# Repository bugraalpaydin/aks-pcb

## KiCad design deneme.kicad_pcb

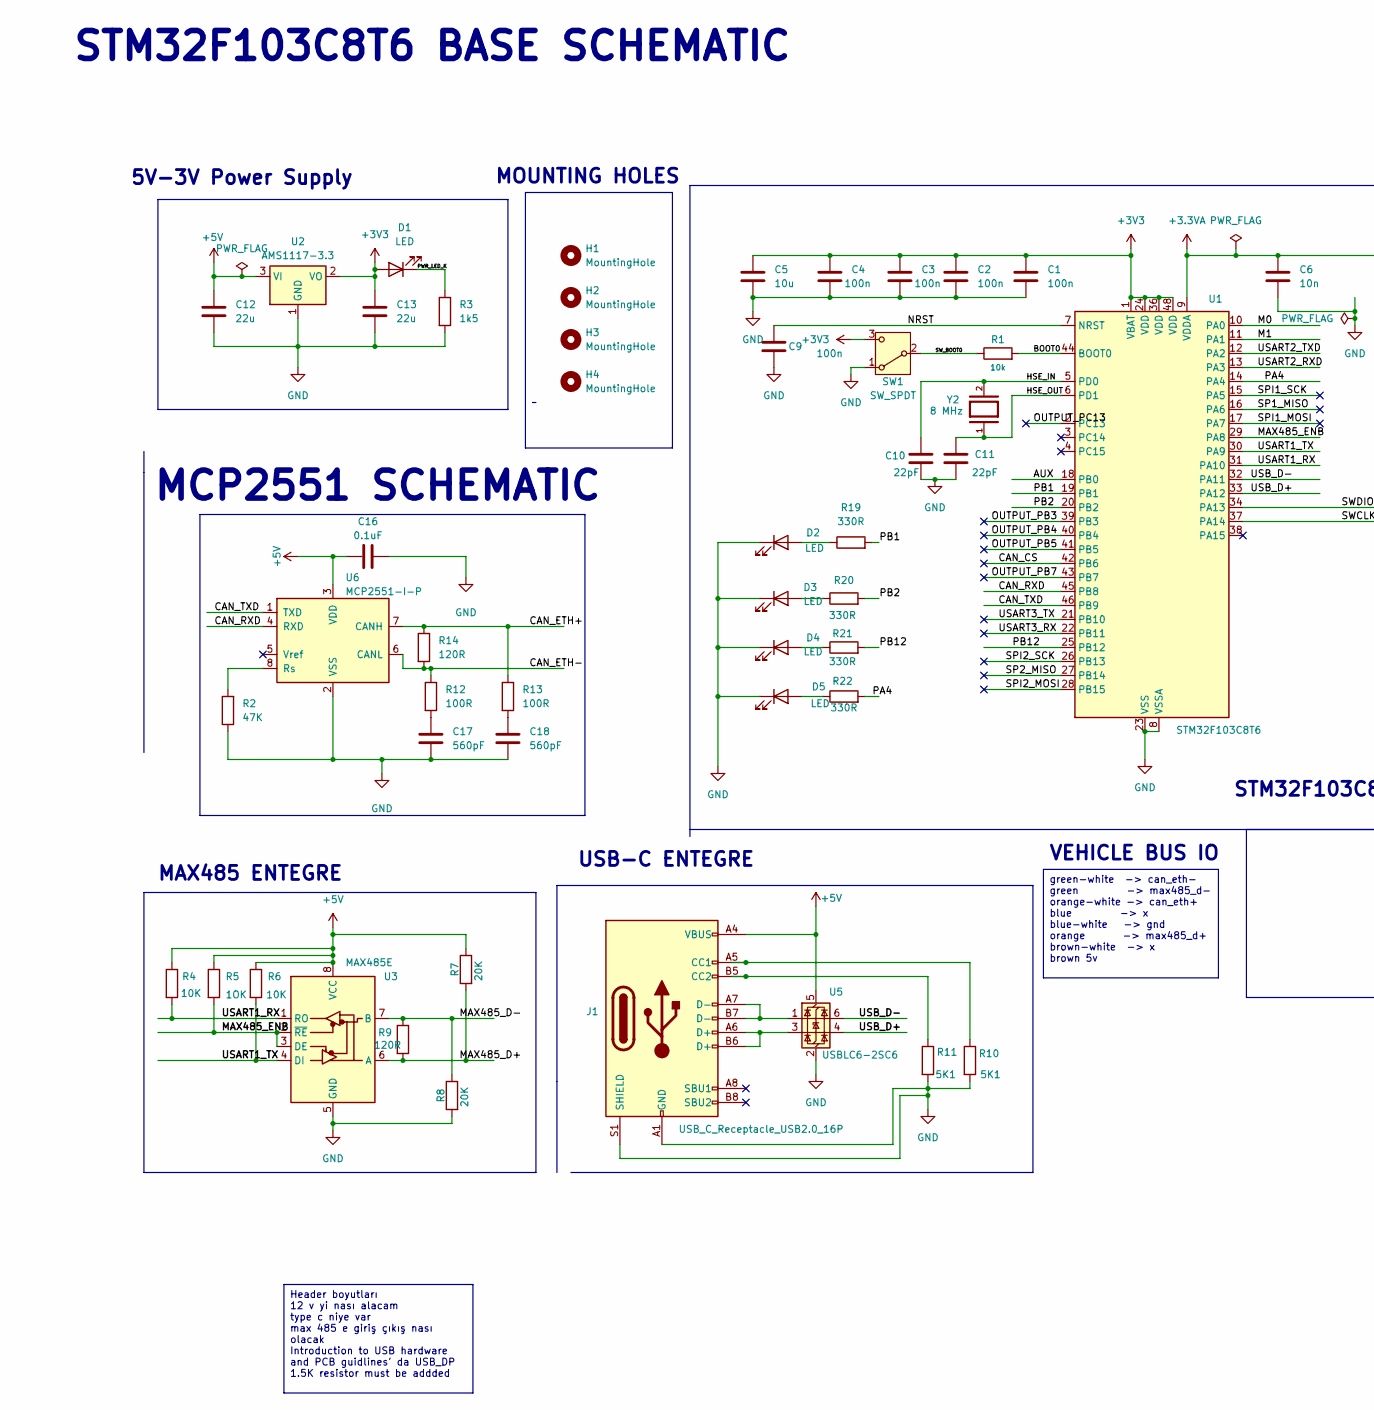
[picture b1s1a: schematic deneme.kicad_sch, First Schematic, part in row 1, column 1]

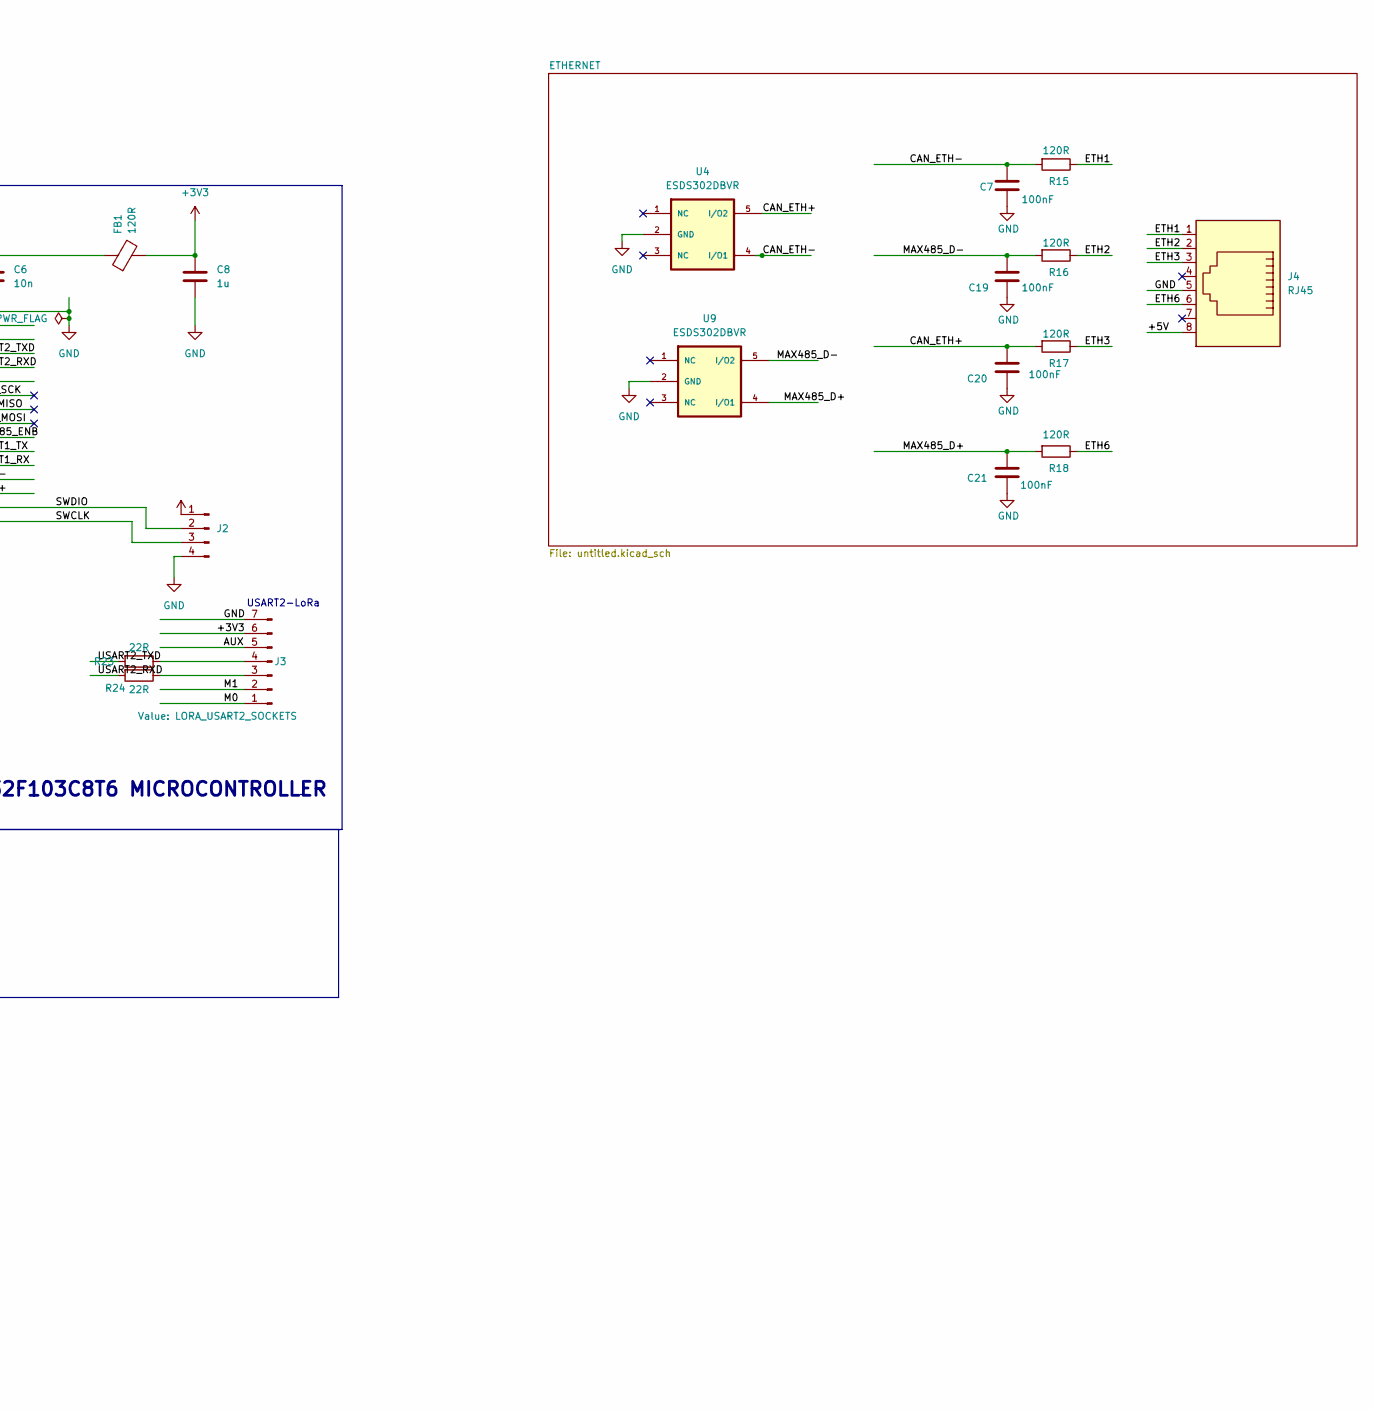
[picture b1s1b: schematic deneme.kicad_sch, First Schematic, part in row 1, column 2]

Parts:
C1, C2, C3, C4, C9: 100n; C_1206_3216Metric
C5: 10u; C_1206_3216Metric
C6: 10n; C_1206_3216Metric
C7, C19, C20, C21: 100nF; C_1206_3216Metric
C8: 1u; C_1206_3216Metric
C10, C11: 22pF; C_1206_3216Metric
C12, C13: 22u; C_1206_3216Metric
C16: 0.1uF; C_1206_3216Metric
C17, C18: 560pF; C_1206_3216Metric
D1, D2, D3, D4, D5: LED; LED_1206_3216Metric
FB1: 120R; L_1206_3216Metric
H1, H2, H3, H4: MountingHole; MountingHole_2.1mm
J1: USB_C_Receptacle_USB2.0_16P; USB-C
J2: Conn_01x04_Pin; PinHeader_1x04_P2.54mm_Vertical
J3: LORA_USART2_SOCKETS; PinSocket_1x07_P2.54mm_Vertical
J4: RJ45; RJ45_Amphenol_RJHSE538X
R1: 10k; R_1206_3216Metric
R2: 47K; R_1206_3216Metric
R3: 1k5; R_1206_3216Metric
R4, R6: 10K; R_1206_3216Metric
R5: 1OK; R_1206_3216Metric
R7, R8: 20K; R_1206_3216Metric
R9, R14: 120R; R_1206_3216Metric
R10, R11: 5K1; R_1206_3216Metric
R12, R13: 100R; R_1206_3216Metric
R15, R16, R17, R18: 120R; C_1206_3216Metric
R19, R20, R21, R22: 330R; R_1206_3216Metric
R23, R24: 22R; R_1206_3216Metric
SW1: SW_SPDT; SW_CK_JS202011CQN_DPDT_Straight
U1: STM32F103C8T6; LQFP-48_7x7mm_P0.5mm
U2: AMS1117-3.3; SOT-223-3_TabPin2
U3: MAX485E; DIP-8_W8.89mm_SMDSocket_LongPads
U4, U9: ESDS302DBVR; ESDS302
U5: USBLC6-2SC6; SOT-23-6
U6: MCP2551-I-P; DIP-8_W7.62mm
Y2: 8 MHz; XTAL_HC49P488W43L1150T466H350; PARTREV 1.0

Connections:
+3.3VA: C6.1, FB1.1, U1.9 (VDDA)
+3V3: C1.1, C2.1, C3.1, C4.1, C5.1, C8.1, C13.1, D1.2 (A), FB1.2, J2.1, J3.6, SW1.3 (C), U1.1 (VBAT), U1.24 (VDD), U1.36 (VDD), U1.48 (VDD), U2.2 (VO)
+5V: C12.1, C16.1, J1.A4 (VBUS), J1.A9 (VBUS), J1.B4 (VBUS), J1.B9 (VBUS), J4.8, R4.1, R5.1, R6.1, R7.1, U2.3 (VI), U3.8 (VCC), U5.5 (VBUS), U6.3 (VDD)
/AUX: J3.5, U1.18 (PB0)
/BOOT0: R1.2, U1.44 (BOOT0)
/CAN_CS: U1.42 (PB6)
/CAN_ETH+: C20.1, R13.1, R14.1, R17.2, U4.5 (I/O2), U6.7 (CANH)
/CAN_ETH-: C7.1, R12.1, R14.2, R15.2, U4.4 (I/O1), U6.6 (CANL)
/CAN_RXD: U1.45 (PB8), U6.4 (RXD)
/CAN_TXD: U1.46 (PB9), U6.1 (TXD)
/ETH1: J4.1, R15.1
/ETH2: J4.2, R16.1
/ETH3: J4.3, R17.1
/ETH6: J4.6, R18.1
/HSE_IN: C10.1, U1.5 (PD0), Y2.2
/HSE_OUT: C11.1, U1.6 (PD1), Y2.1
/M0: J3.1, U1.10 (PA0)
/M1: J3.2, U1.11 (PA1)
/MAX485_D+: C21.1, R7.2, R9.2, R18.2, U3.6 (A), U9.4 (I/O1)
/MAX485_D-: C19.1, R8.1, R9.1, R16.2, U3.7 (B), U9.5 (I/O2)
/MAX485_ENB: R5.2, U1.29 (PA8), U3.2 (~RE), U3.3 (DE)
/NRST: C9.1, U1.7 (NRST)
/OUTPUT_PB3: U1.39 (PB3)
/OUTPUT_PB4: U1.40 (PB4)
/OUTPUT_PB5: U1.41 (PB5)
/OUTPUT_PB7: U1.43 (PB7)
/OUTPUT_PC13: U1.2 (PC13)
/PA4: R22.2, U1.14 (PA4)
/PB1: R19.2, U1.19 (PB1)
/PB2: R20.2, U1.20 (PB2)
/PB12: R21.2, U1.25 (PB12)
/PWR_LED_K: D1.1 (K), R3.1
/SP1_MISO: U1.16 (PA6)
/SP2_MISO: U1.27 (PB14)
/SPI1_MOSI: U1.17 (PA7)
/SPI1_SCK: U1.15 (PA5)
/SPI2_MOSI: U1.28 (PB15)
/SPI2_SCK: U1.26 (PB13)
/SWCLK: J2.3, U1.37 (PA14)
/SWDIO: J2.2, U1.34 (PA13)
/SW_BOOT0: R1.1, SW1.2 (B)
/USART1_RX: R4.2, U1.31 (PA10), U3.1 (RO)
/USART1_TX: R6.2, U1.30 (PA9), U3.4 (DI)
/USART2_RXD: R24.2, U1.13 (PA3)
/USART2_TXD: R23.2, U1.12 (PA2)
/USART3_RX: U1.22 (PB11)
/USART3_TX: U1.21 (PB10)
/USB_D+: U1.33 (PA12), U5.4 (I/O2)
/USB_D-: U1.32 (PA11), U5.6 (I/O1)
GND: C1.2, C2.2, C3.2, C4.2, C5.2, C6.2, C7.2, C8.2, C9.2, C10.2, C11.2, C12.2, C13.2, C16.2, C17.2, C18.2, C19.2, C20.2, C21.2, D2.1 (K), D3.1 (K), D4.1 (K), D5.1 (K), J1.A1 (GND), J1.A12 (GND), J1.B1 (GND), J1.B12 (GND), J1.S1 (SHIELD), J2.4, J3.7, J4.5, R2.1, R3.2, R8.2, R10.2, R11.2, SW1.1 (A), U1.8 (VSSA), U1.23 (VSS), U1.35 (VSS), U1.47 (VSS), U2.1 (GND), U3.5 (GND), U4.2 (GND), U5.2 (GND), U6.2 (VSS), U9.2 (GND)
unnamed: C17.1, R12.2
unnamed: C18.1, R13.2
unnamed: D2.2 (A), R19.1
unnamed: D3.2 (A), R20.1
unnamed: D4.2 (A), R21.1
unnamed: D5.2 (A), R22.1
unnamed: J1.A5 (CC1), R10.1
unnamed: J1.B5 (CC2), R11.1
unnamed: J1.A6 (D+), J1.B6 (D+), U5.3 (I/O2)
unnamed: J1.A7 (D-), J1.B7 (D-), U5.1 (I/O1)
unnamed: J3.3, R24.1
unnamed: J3.4, R23.1
unnamed: R2.2, U6.8 (Rs)

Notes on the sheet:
green-white -> can_eth- green -> max485_d- orange-white -> can_eth+ blue -> x blue-white -> gnd orange -> max485_d+ brown-white -> x brown 5v
Header boyutları 12 v yi nası alacam type c niye var max 485 e giriş çıkış nası olacak Introduction to USB hardware and PCB guidlines' da USB_DP 1.5K resistor must be addded
5V-3V Power Supply
USB-C ENTEGRE
VEHICLE BUS IO
STM32F103C8T6 BASE SCHEMATIC
MOUNTING HOLES
MAX485 ENTEGRE
STM32F103C8T6 MICROCONTROLLER
USART2-LoRa
MCP2551 SCHEMATIC

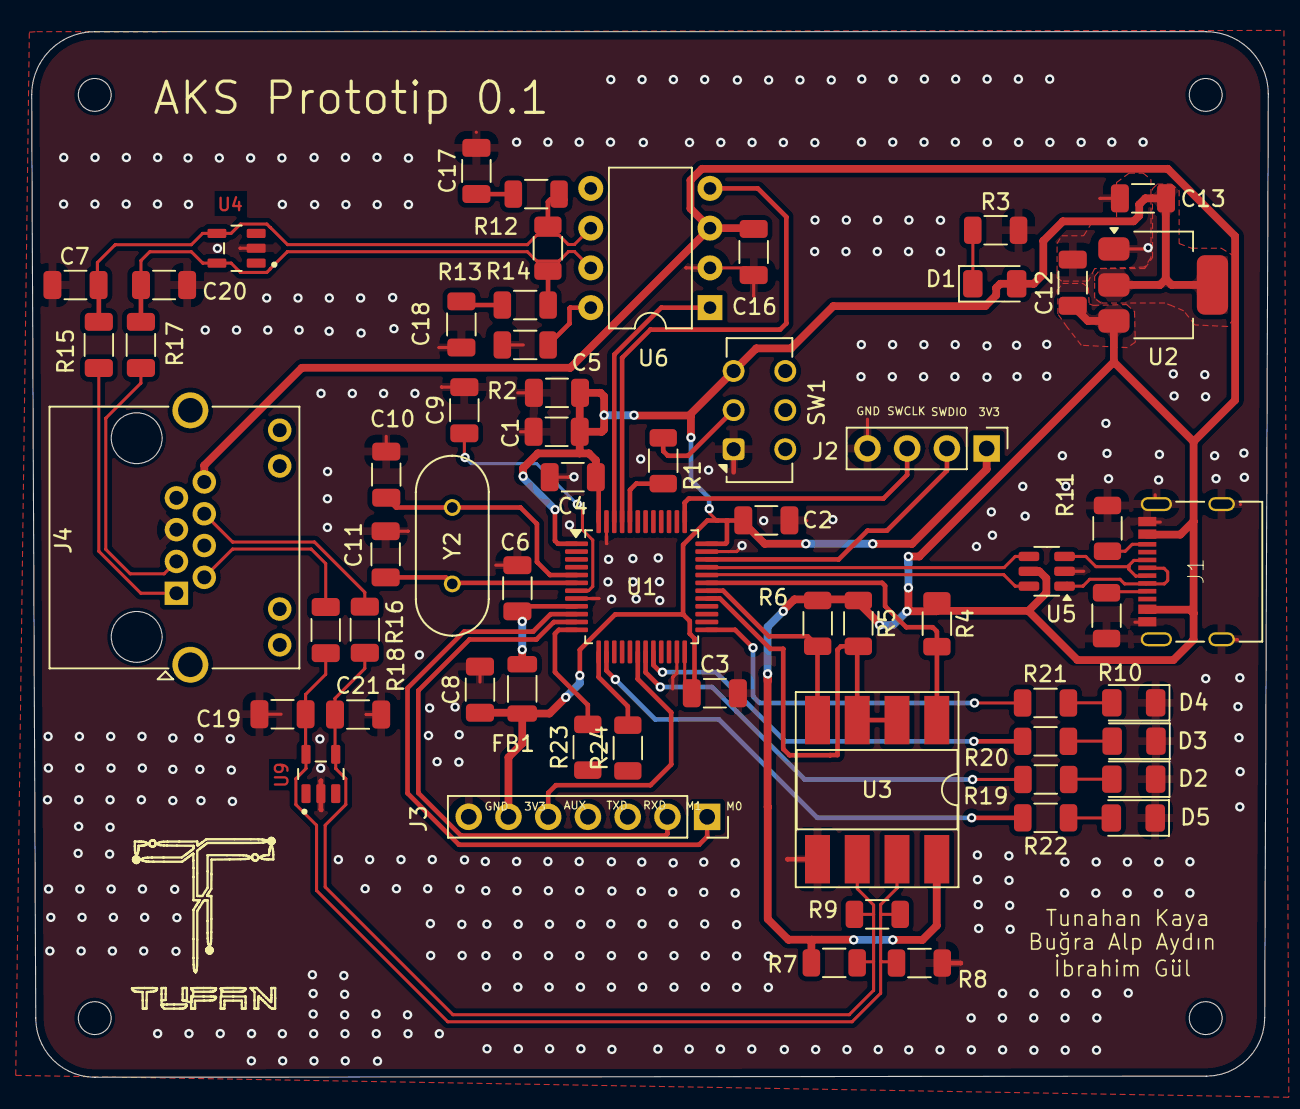
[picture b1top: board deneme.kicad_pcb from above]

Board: 2 copper layers, 79.0 x 66.8 mm, 69 parts (0 on the bottom side), 49 nets.

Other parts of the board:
H1#2, H1#3, H1#4: MountingHole; MountingHole_2.1mm

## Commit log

2024-05-02 uretim
2024-05-08 added manufacturing files
2024-05-09 added led resistors
2024-06-05 Added Ibrahım Gul's name to the board
